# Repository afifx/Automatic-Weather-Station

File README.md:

# Automatic-Weather-Station
Repository Low Power Automatic Weather System

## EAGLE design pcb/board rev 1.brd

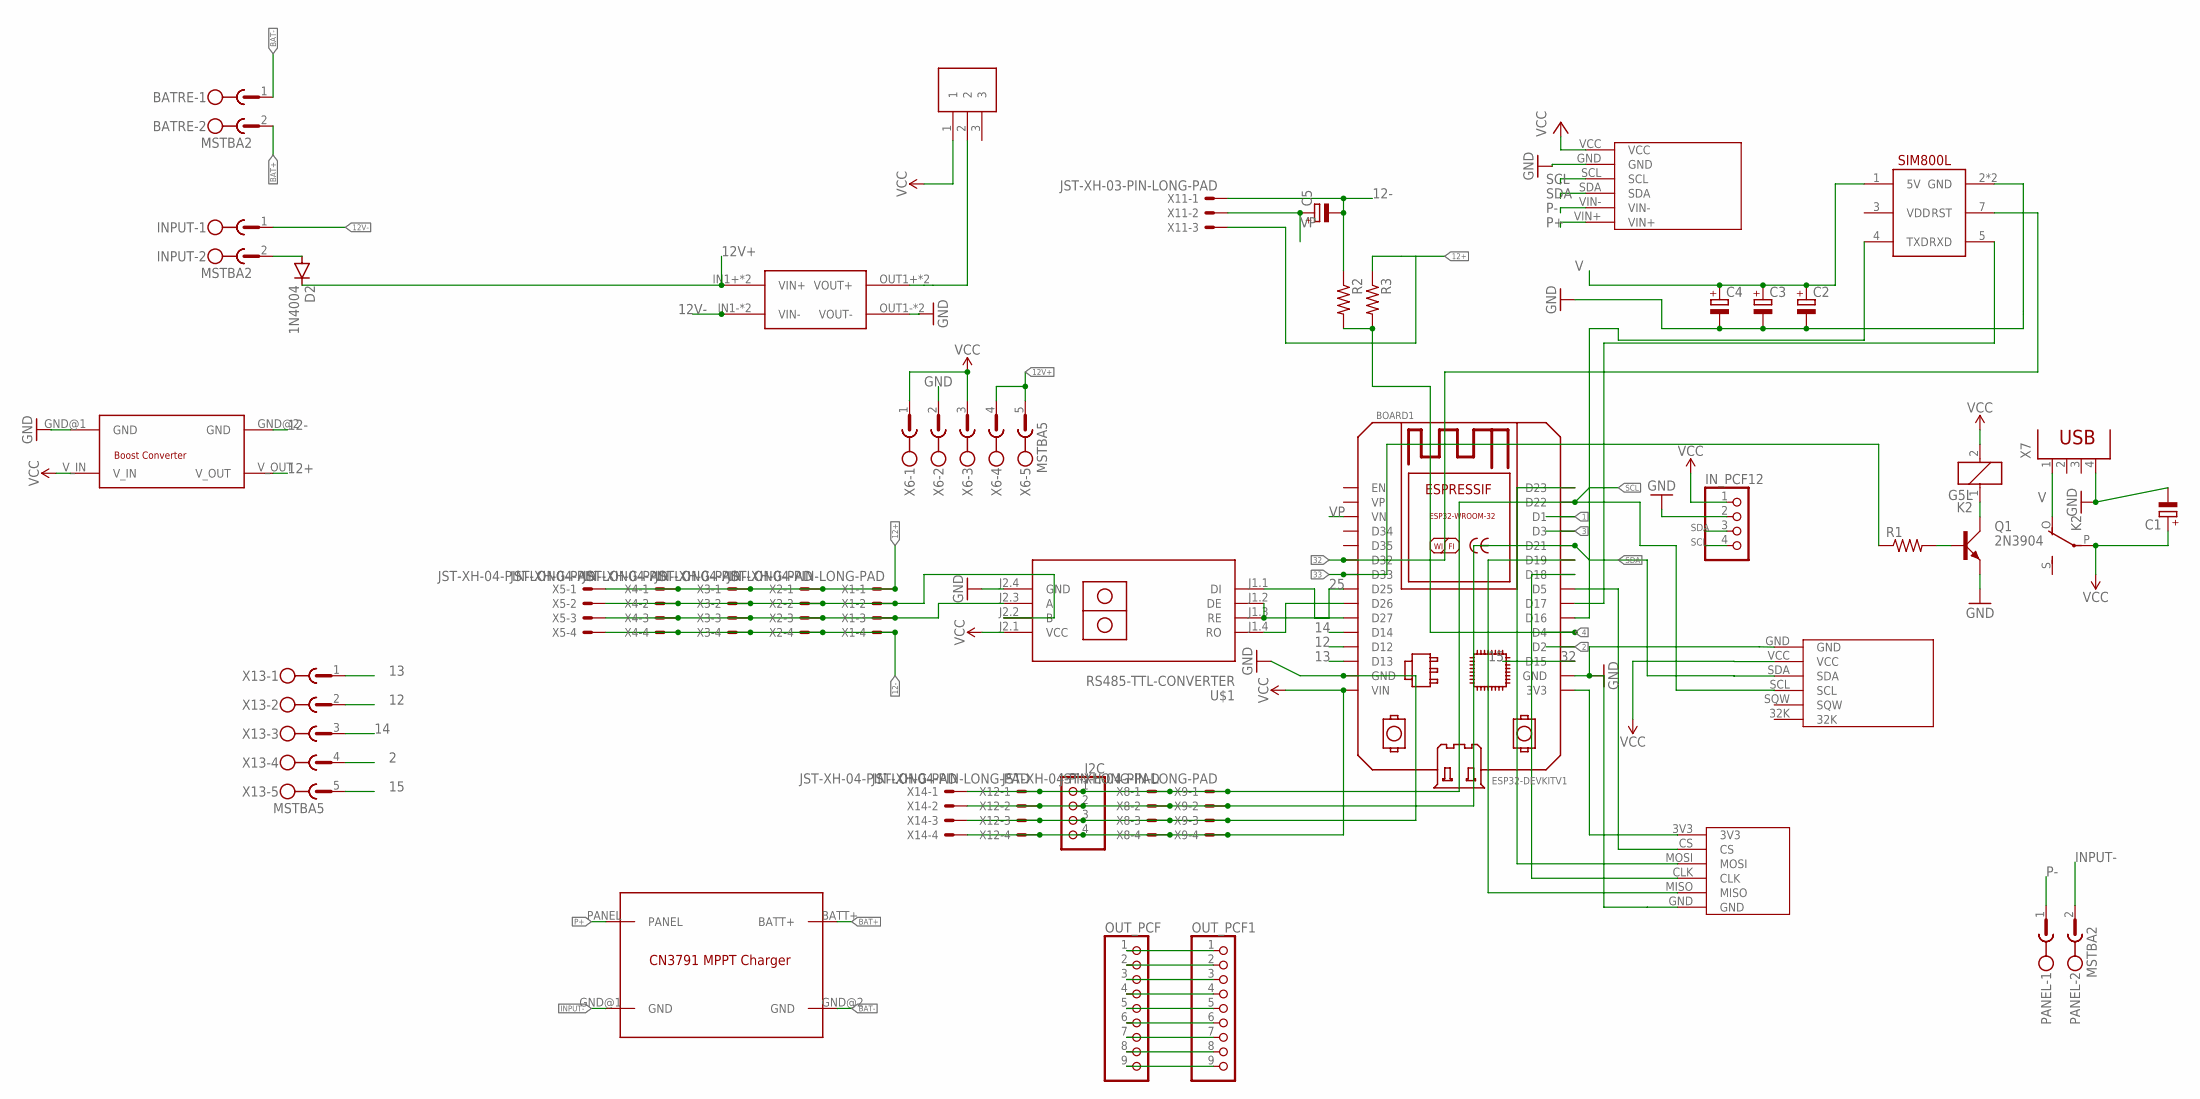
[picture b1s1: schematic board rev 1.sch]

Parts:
BATRE: MSTBA2
BOARD1: ESP32DEVKITV1; ESP32-DEVKITV1
C1, C2, C3, C4, C5: CPOL-EUE2.5-7; E2,5-7
D2: 1N4004; DO41-10
I2C: PINHD-1X4; 1X04
INPUT: MSTBA2
IN_PCF12: PINHD-1X4; 1X04
K2: G5L; G5LE
OUT_PCF, OUT_PCF1: PINHD-1X9; 1X09
PANEL: MSTBA2
Q1: 2N3904; TO92D
R1, R2, R3: R-US_0204/7; 0204/7
SW1: SS12D10
U$1: RS485-TTL-CONVERTER
U$2: CN3791_MTTP_LIPO_SOLAR_CHARGER; CN3791_MPPT_LIPO_SOLAR_CHARGER
U$3: MP1584; DC-BRICK
U$4: SIM800L; SIP
U$5: ICSA004A_BOOST_MODULE
U$6: DS3231
U$7: MICROSD3V3
U$8: INA219
X1, X2, X3, X4, X5, X8, X9, X12, X14: JST-XH-04-PIN-LONG-PAD; JST-XH-04-PACKAGE-LONG-PAD
X6, X13: MSTBA5
X7: PN87520
X11: JST-XH-03-PIN-LONG-PAD; JST-XH-03-PACKAGE-LONG-PAD

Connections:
1: BOARD1.D1
2: BOARD1.D2, X13.4
3: BOARD1.D3
4: BOARD1.D4, R2.2, R3.2
12: BOARD1.D12, X13.2
12+: R3.1, U$5.V_OUT, X1.1, X2.1, X3.1, X4.1, X5.1, X11.3
12-: C5.-, R2.1, U$5.GND@2 (GND), X1.4, X2.4, X3.4, X4.4, X5.4, X11.1
12V+: D2.C, U$3.IN1+ (VIN+), U$3.IN2+ (VIN+), X6.4, X6.5
12V-: INPUT.1, U$3.IN1- (VIN-), U$3.IN2- (VIN-)
13: BOARD1.D13, X13.1
14: BOARD1.D14, X13.3
15: BOARD1.D15, X13.5
18: BOARD1.D18, U$7.CLK
19: BOARD1.D19, U$7.MISO
25: BOARD1.D25, U$1.J1.2 (DE), U$1.J1.3 (RE)
32: BOARD1.D32, U$4.7 (RST)
33: BOARD1.D33, R1.1
BAT+: BATRE.2, U$2.BATT+
BAT-: BATRE.1, U$2.GND@2 (GND)
GND: BOARD1.GND, BOARD1.GND@1 (GND), C1.-, C2.-, C3.-, C4.-, I2C.3, IN_PCF12.2, Q1.E, U$1.J2.4 (GND), U$3.OUT1- (VOUT-), U$3.OUT2- (VOUT-), U$4.2 (GND), U$4.6 (GND), U$5.GND@1 (GND), U$6.GND, U$7.GND, U$8.GND, X6.2, X7.4, X8.3, X9.3, X12.3, X14.3
INPUT-: PANEL.2, U$2.GND@1 (GND)
unnamed: BOARD1.D27, U$1.J1.1 (DI)
unnamed: BOARD1.D26, U$1.J1.4 (RO)
unnamed: OUT_PCF.1, OUT_PCF1.1
unnamed: OUT_PCF.2, OUT_PCF1.2
unnamed: SW1.2, U$3.OUT1+ (VOUT+), U$3.OUT2+ (VOUT+)
unnamed: U$1.J2.2 (B), X1.2, X2.2, X3.2, X4.2, X5.2
unnamed: U$1.J2.3 (A), X1.3, X2.3, X3.3, X4.3, X5.3
unnamed: BOARD1.3V3, U$7.3V3
unnamed: BOARD1.D5, U$7.CS
unnamed: BOARD1.D23, U$7.MOSI
unnamed: D2.A, INPUT.2
unnamed: OUT_PCF.3, OUT_PCF1.3
unnamed: BOARD1.D16, U$4.4 (TXD)
unnamed: BOARD1.D17, U$4.5 (RXD)
unnamed: K2.1, Q1.C
unnamed: OUT_PCF.4, OUT_PCF1.4
unnamed: Q1.B, R1.2
unnamed: OUT_PCF.5, OUT_PCF1.5
unnamed: OUT_PCF.6, OUT_PCF1.6
unnamed: OUT_PCF.7, OUT_PCF1.7
unnamed: OUT_PCF.8, OUT_PCF1.8
unnamed: OUT_PCF.9, OUT_PCF1.9
P+: U$2.PANEL, U$8.VIN+
P-: PANEL.1, U$8.VIN-
SCL: BOARD1.D22, I2C.1, IN_PCF12.4, U$6.SCL, U$8.SCL, X8.1, X9.1, X12.1, X14.1
SDA: BOARD1.D21, I2C.2, IN_PCF12.3, U$6.SDA, U$8.SDA, X8.2, X9.2, X12.2, X14.2
V: C2.+, C3.+, C4.+, K2.O, U$4.1 (5V), X7.1
VCC: BOARD1.VIN, C1.+, I2C.4, IN_PCF12.1, K2.2, K2.P, SW1.1, U$1.J2.1 (VCC), U$5.V_IN, U$6.VCC, U$8.VCC, X6.1, X6.3, X8.4, X9.4, X12.4, X14.4
VP: BOARD1.VN, C5.+, X11.2

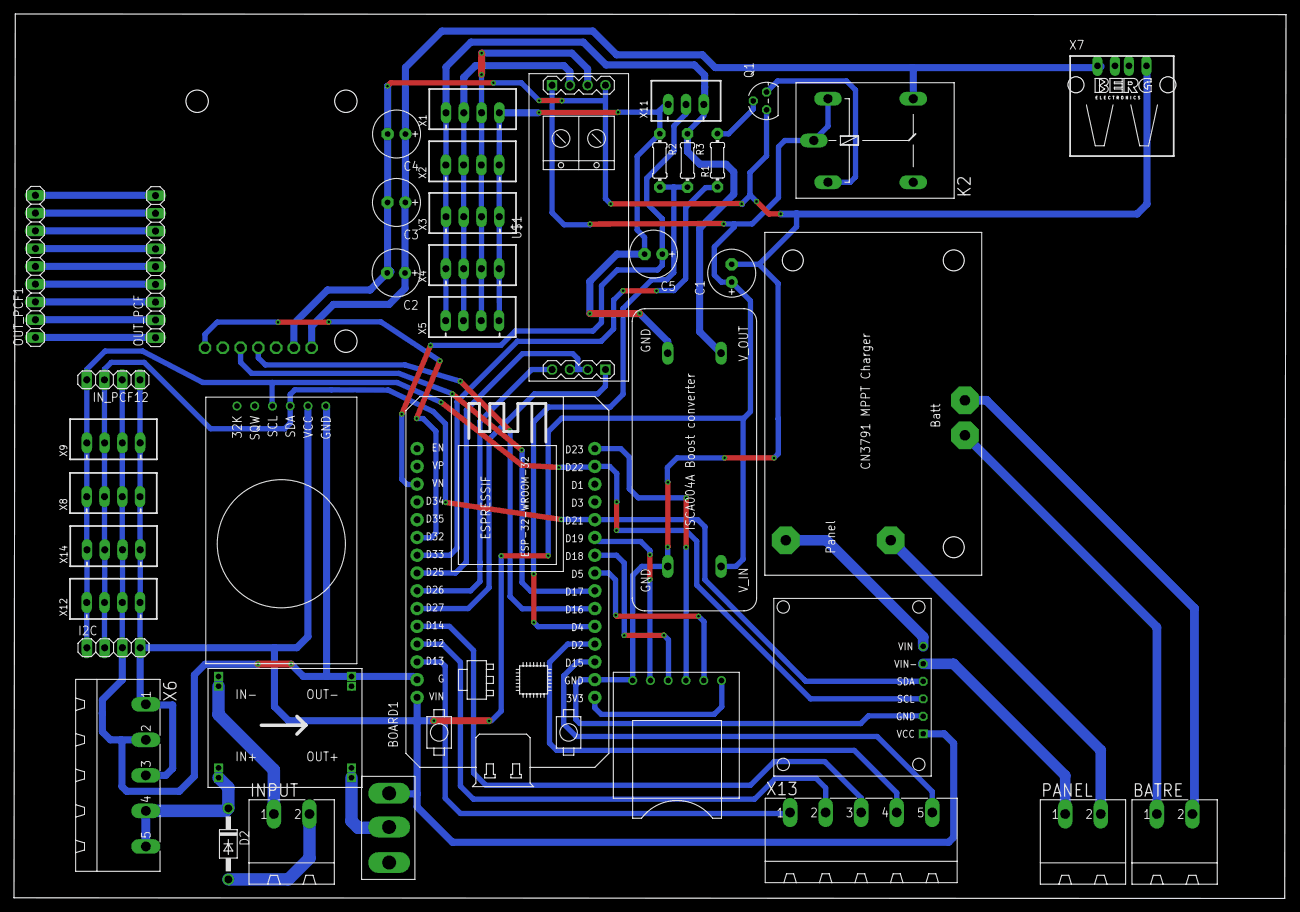
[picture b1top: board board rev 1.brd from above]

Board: 2 copper layers, 181.8 x 126.4 mm, 41 parts (0 on the bottom side), 48 nets.

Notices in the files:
parts and their libraries:
diy: Released under the Creative Commons Attribution 4.0 International License: http://creativecommons.org/licenses/by/4.0
FaBo-Supply: Released under the Creative Commons Attribution-ShareAlike 4.0 License
https://creativecommons.org/licenses/by-sa/4.0
